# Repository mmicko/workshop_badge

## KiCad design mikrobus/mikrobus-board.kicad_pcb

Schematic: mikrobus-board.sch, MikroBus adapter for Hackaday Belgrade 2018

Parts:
J1: Conn_01x06; Pin_Header_Straight_1x06_Pitch2.54mm
P3, P5: microBus_1; Socket_Strip_Straight_1x08_Pitch2.54mm
P4, P6: microBus_2; Socket_Strip_Straight_1x08_Pitch2.54mm
UPDUINO2_DOWN1: Conn_01x16; Socket_Strip_Straight_1x16_Pitch2.54mm
UPDUINO2_UP1: Conn_01x18; Socket_Strip_Straight_1x18_Pitch2.54mm

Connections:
+3V3: J1.5, P3.7, P5.7, UPDUINO2_DOWN1.16
/AN_1: P3.1, UPDUINO2_UP1.1
/AN_2: P5.1, UPDUINO2_DOWN1.1
/CS_1: P3.3, UPDUINO2_UP1.6
/CS_2: P5.3, UPDUINO2_DOWN1.3
/EXT_1: J1.4, UPDUINO2_UP1.13
/EXT_2: J1.3, UPDUINO2_UP1.14
/EXT_3: J1.2, UPDUINO2_UP1.15
/EXT_4: J1.1, UPDUINO2_UP1.16
/INT_1: P4.2, UPDUINO2_UP1.8
/INT_2: P6.2, UPDUINO2_DOWN1.10
/MISO_1: P3.5, UPDUINO2_UP1.4
/MISO_2: P5.5, UPDUINO2_DOWN1.5
/MOSI_1: P3.6, UPDUINO2_UP1.3
/MOSI_2: P5.6, UPDUINO2_DOWN1.6
/OSC_OUT: UPDUINO2_DOWN1.9, UPDUINO2_UP1.17
/PWM_1: P4.1, UPDUINO2_UP1.7
/PWM_2: P6.1, UPDUINO2_DOWN1.8
/RST_1: P3.2, UPDUINO2_UP1.2
/RST_2: P5.2, UPDUINO2_DOWN1.2
/RX_1: P4.3, UPDUINO2_UP1.9
/RX_2: P6.3, UPDUINO2_DOWN1.11
/SCK_1: P3.4, UPDUINO2_UP1.5
/SCK_2: P5.4, UPDUINO2_DOWN1.4
/SCL_1: P4.5, UPDUINO2_UP1.11
/SCL_2: P6.5, UPDUINO2_DOWN1.13
/SDA_1: P4.6, UPDUINO2_UP1.12
/SDA_2: P6.6, UPDUINO2_DOWN1.14
/TX_1: P4.4, UPDUINO2_UP1.10
/TX_2: P6.4, UPDUINO2_DOWN1.12
GND: J1.6, P3.8, P4.8, P5.8, P6.8, UPDUINO2_DOWN1.15, UPDUINO2_UP1.18

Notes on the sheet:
mikroBus 1
mikroBus 2

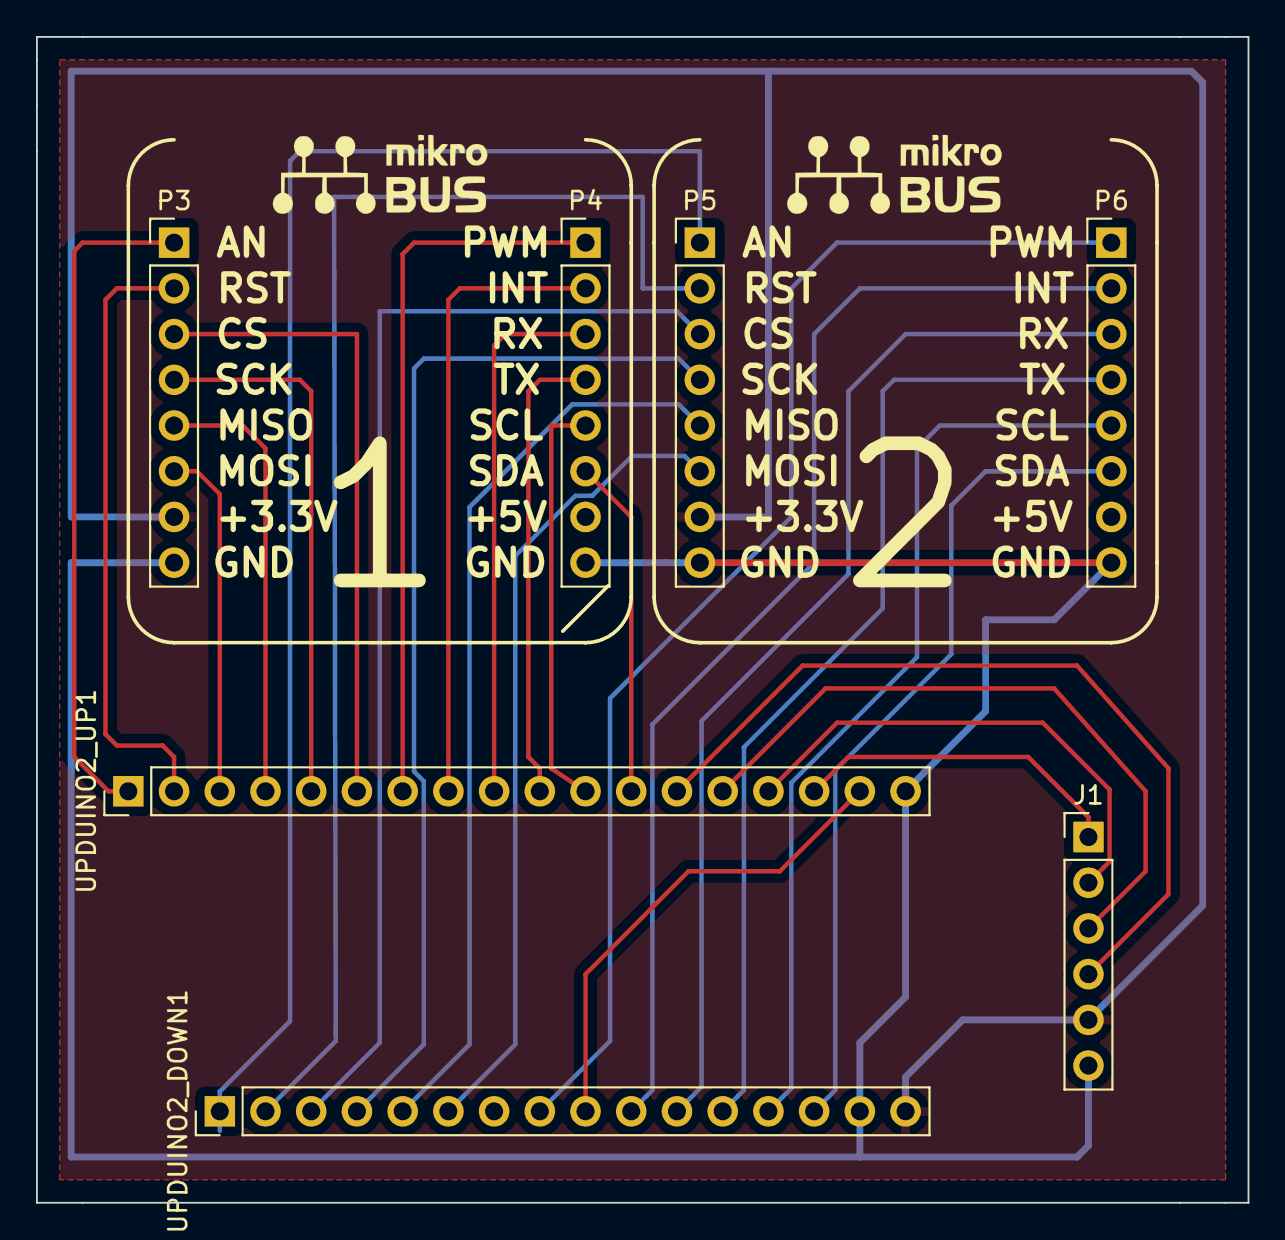
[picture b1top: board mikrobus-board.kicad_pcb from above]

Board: 2 copper layers, 67.3 x 64.8 mm, 9 parts (0 on the bottom side), 31 nets.

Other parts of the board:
G1, G1#2: LOGO; mikrobus

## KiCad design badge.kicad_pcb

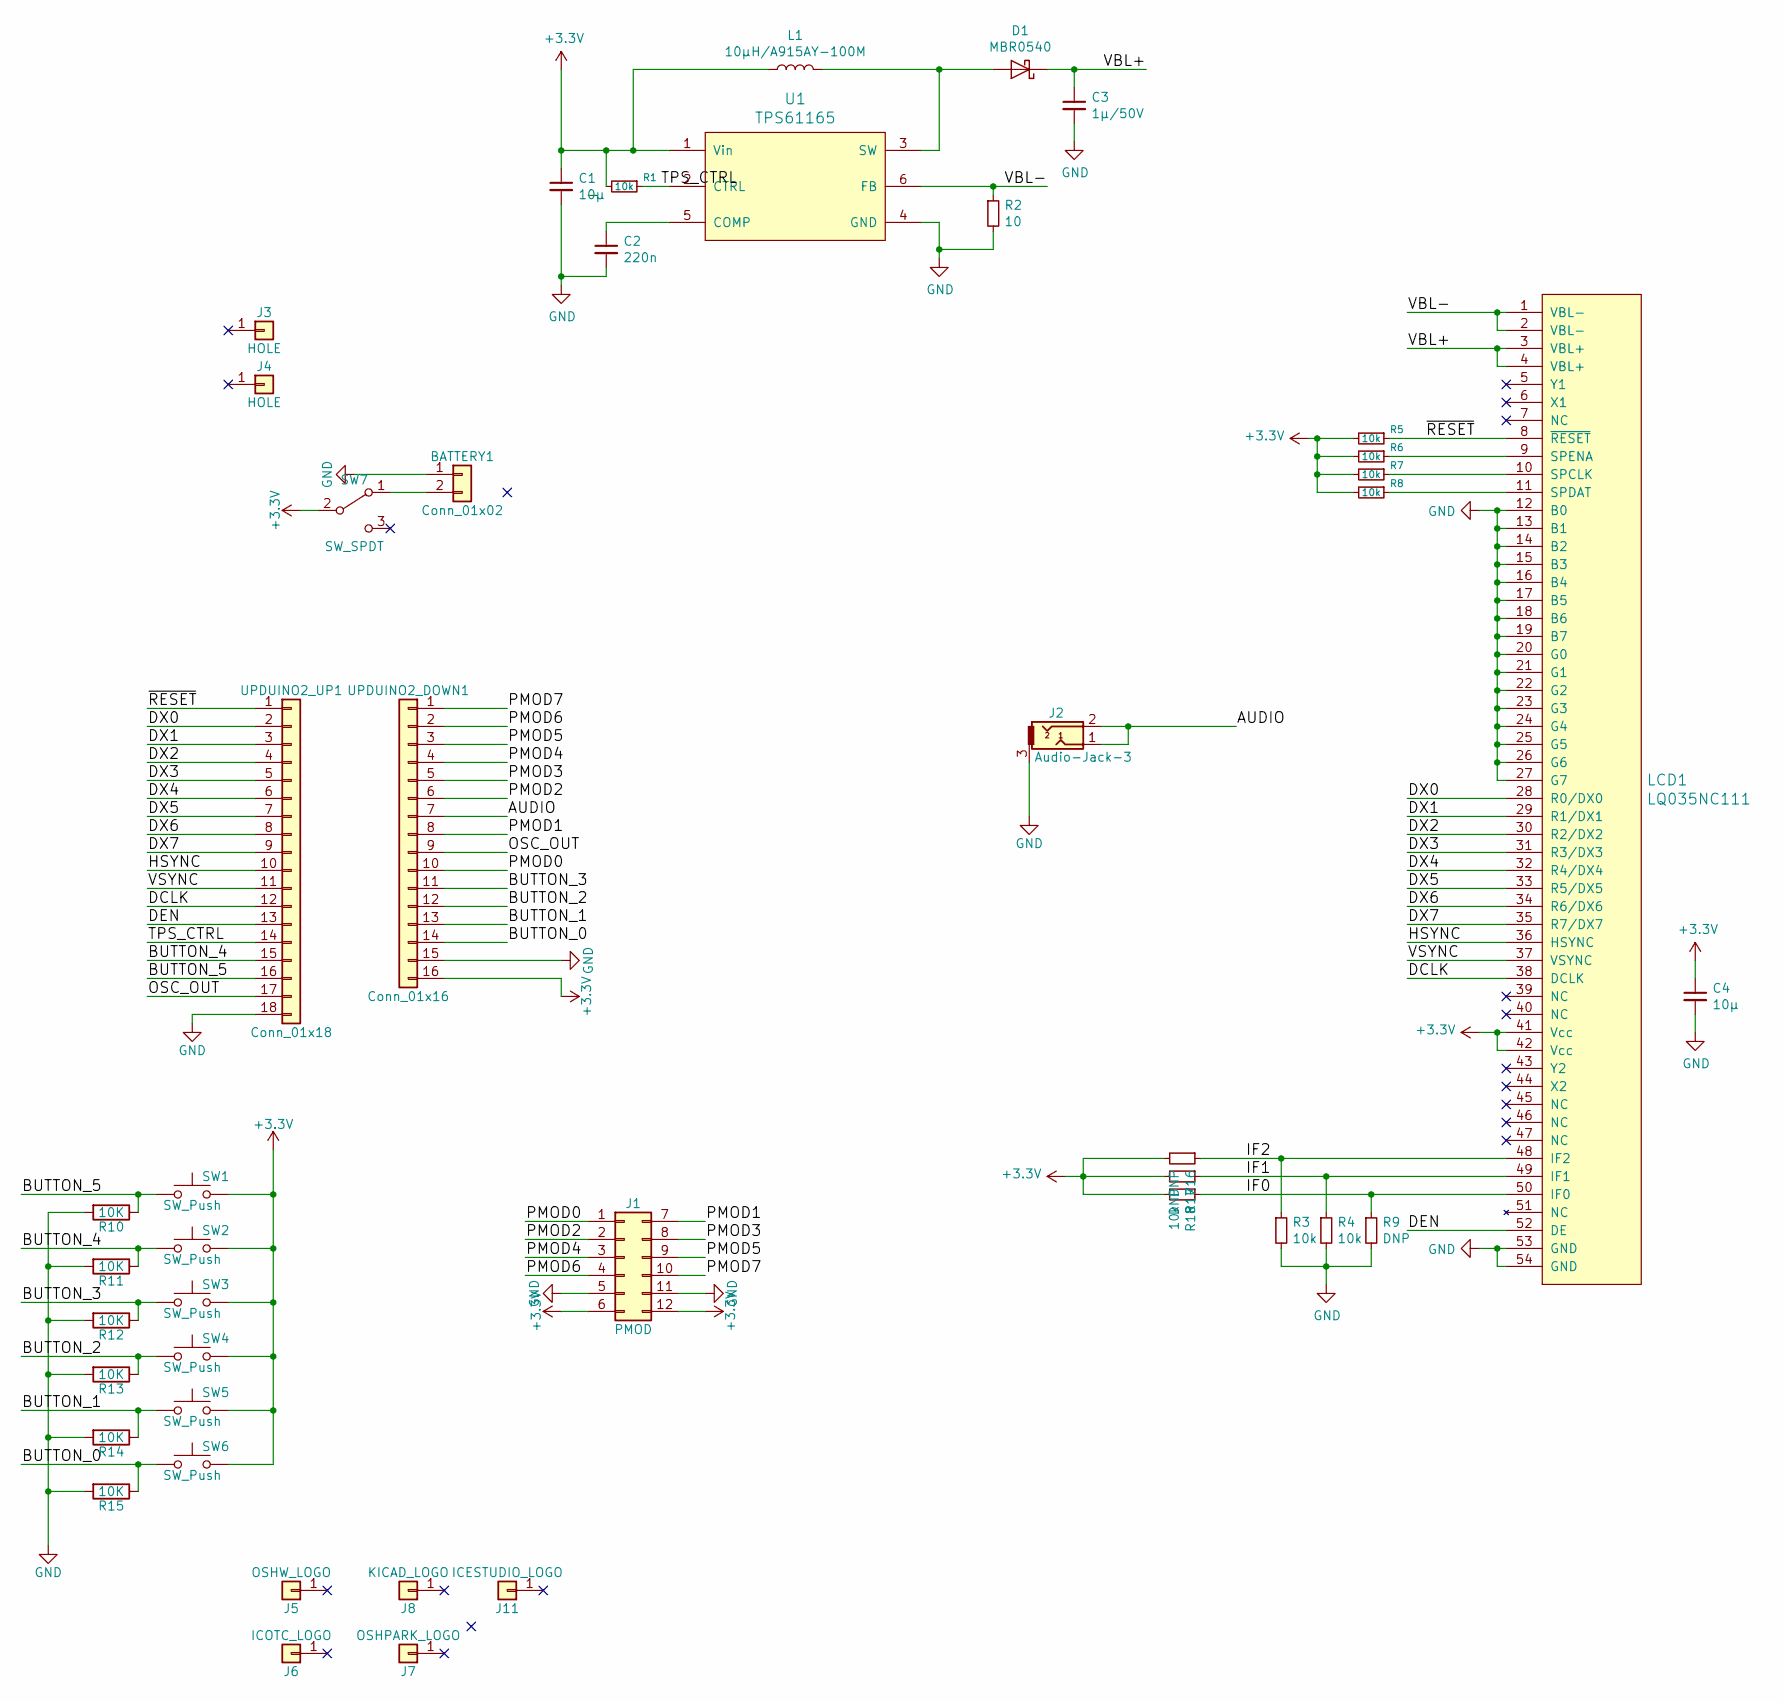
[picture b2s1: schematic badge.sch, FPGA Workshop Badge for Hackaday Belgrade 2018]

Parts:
BATTERY1: Conn_01x02; Pin_Header_Straight_1x02_Pitch2.54mm
C1, C4: 10µ; C_0805
C2: 220n; C_0603
C3: 1µ/50V; C_0805
D1: MBR0540; D_SOD-123
J1: PMOD; Pin_Header_Angled_2x06_Pitch2.54mm_PMOD
J2: Audio-Jack-3; AUDIO_JACK_3.5mm
J3, J4: HOLE; MountingHole_3.2mm_M3
J5: OSHW_LOGO; OSHW-Logo2_24.3x20mm_SilkScreen
J6: ICOTC_LOGO; ICOTC
J7: OSHPARK_LOGO; OSHPARK
J8: KICAD_LOGO; KiCad-Logo_12mm_SilkScreen
J11: ICESTUDIO_LOGO; ICESTUDIO
L1: 10µH/A915AY-100M; muRata_L_2020
LCD1: LQ035NC111; MOLEX_51296-5494_54pin_0.5mm_BTM
R1, R3, R4, R5, R6, R7, R8, R18: 10k; R_0603
R2: 10; R_0603
R9, R16, R17: DNP; R_0603
R10, R11, R12, R13, R14, R15: 10K; R_0603
SW1, SW2, SW3, SW4, SW5, SW6: SW_Push; SW_PUSH-12mm
SW7: SW_SPDT; SW_CuK_OS102011MA1QN1_SPDT_Angled
U1: TPS61165; SOT-23-6
UPDUINO2_DOWN1: Conn_01x16; Pin_Header_Straight_1x16_Pitch2.54mm
UPDUINO2_UP1: Conn_01x18; Pin_Header_Straight_1x18_Pitch2.54mm

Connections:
+3V3: C1.1, C4.1, J1.6, J1.12, L1.1, LCD1.41 (Vcc), LCD1.42 (Vcc), R1.2, R5.2, R6.2, R7.2, R8.2, R16.2, R17.2, R18.2, SW1.2, SW2.2, SW3.2, SW4.2, SW5.2, SW6.2, SW7.2 (B), U1.1 (Vin), UPDUINO2_DOWN1.16
/AUDIO: J2.1, J2.2, UPDUINO2_DOWN1.7
/BUTTON_0: R15.1, SW6.1, UPDUINO2_DOWN1.14
/BUTTON_1: R14.1, SW5.1, UPDUINO2_DOWN1.13
/BUTTON_2: R13.1, SW4.1, UPDUINO2_DOWN1.12
/BUTTON_3: R12.1, SW3.1, UPDUINO2_DOWN1.11
/BUTTON_4: R11.1, SW2.1, UPDUINO2_UP1.15
/BUTTON_5: R10.1, SW1.1, UPDUINO2_UP1.16
/DCLK: LCD1.38 (DCLK), UPDUINO2_UP1.12
/DEN: LCD1.52 (DE), UPDUINO2_UP1.13
/DX0: LCD1.28 (R0/DX0), UPDUINO2_UP1.2
/DX1: LCD1.29 (R1/DX1), UPDUINO2_UP1.3
/DX2: LCD1.30 (R2/DX2), UPDUINO2_UP1.4
/DX3: LCD1.31 (R3/DX3), UPDUINO2_UP1.5
/DX4: LCD1.32 (R4/DX4), UPDUINO2_UP1.6
/DX5: LCD1.33 (R5/DX5), UPDUINO2_UP1.7
/DX6: LCD1.34 (R6/DX6), UPDUINO2_UP1.8
/DX7: LCD1.35 (R7/DX7), UPDUINO2_UP1.9
/HSYNC: LCD1.36 (HSYNC), UPDUINO2_UP1.10
/IF0: LCD1.50 (IF0), R9.1, R18.1
/IF1: LCD1.49 (IF1), R4.1, R17.1
/IF2: LCD1.48 (IF2), R3.1, R16.1
/OSC_OUT: UPDUINO2_DOWN1.9, UPDUINO2_UP1.17
/PMOD0: J1.1, UPDUINO2_DOWN1.10
/PMOD1: J1.7, UPDUINO2_DOWN1.8
/PMOD2: J1.2, UPDUINO2_DOWN1.6
/PMOD3: J1.8, UPDUINO2_DOWN1.5
/PMOD4: J1.3, UPDUINO2_DOWN1.4
/PMOD5: J1.9, UPDUINO2_DOWN1.3
/PMOD6: J1.4, UPDUINO2_DOWN1.2
/PMOD7: J1.10, UPDUINO2_DOWN1.1
/TPS_CTRL: R1.1, U1.2 (CTRL), UPDUINO2_UP1.14
/VBL+: C3.1, D1.1 (K), LCD1.3 (VBL+), LCD1.4 (VBL+)
/VBL-: LCD1.1 (VBL-), LCD1.2 (VBL-), R2.1, U1.6 (FB)
/VSYNC: LCD1.37 (VSYNC), UPDUINO2_UP1.11
/~RESET: LCD1.8 (~RESET), R5.1, UPDUINO2_UP1.1
GND: BATTERY1.1, C1.2, C2.2, C3.2, C4.2, J1.5, J1.11, J2.3, LCD1.12 (B0), LCD1.13 (B1), LCD1.14 (B2), LCD1.15 (B3), LCD1.16 (B4), LCD1.17 (B5), LCD1.18 (B6), LCD1.19 (B7), LCD1.20 (G0), LCD1.21 (G1), LCD1.22 (G2), LCD1.23 (G3), LCD1.24 (G4), LCD1.25 (G5), LCD1.26 (G6), LCD1.27 (G7), LCD1.53 (GND), LCD1.54 (GND), R2.2, R3.2, R4.2, R9.2, R10.2, R11.2, R12.2, R13.2, R14.2, R15.2, U1.4 (GND), UPDUINO2_DOWN1.15, UPDUINO2_UP1.18
unnamed: BATTERY1.2, SW7.1 (A)
unnamed: C2.1, U1.5 (COMP)
unnamed: D1.2 (A), L1.2, U1.3 (SW)
unnamed: LCD1.9 (SPENA), R6.1
unnamed: LCD1.10 (SPCLK), R7.1
unnamed: LCD1.11 (SPDAT), R8.1

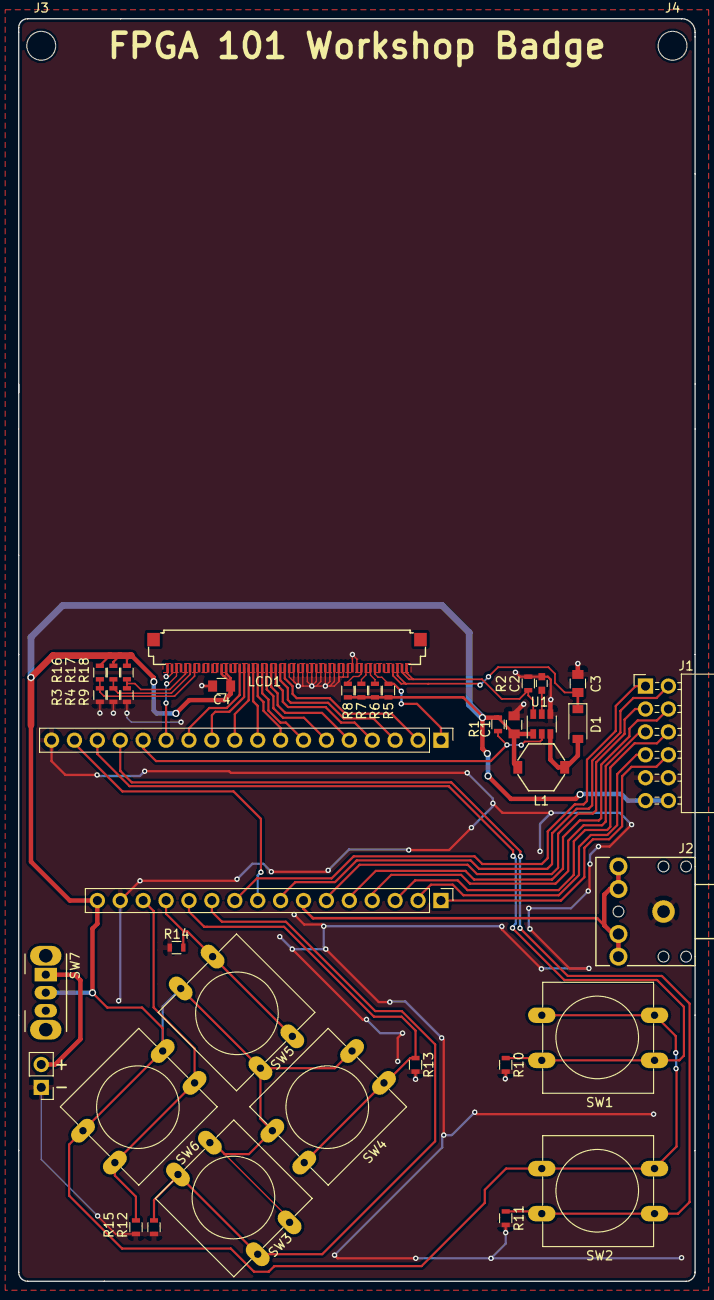
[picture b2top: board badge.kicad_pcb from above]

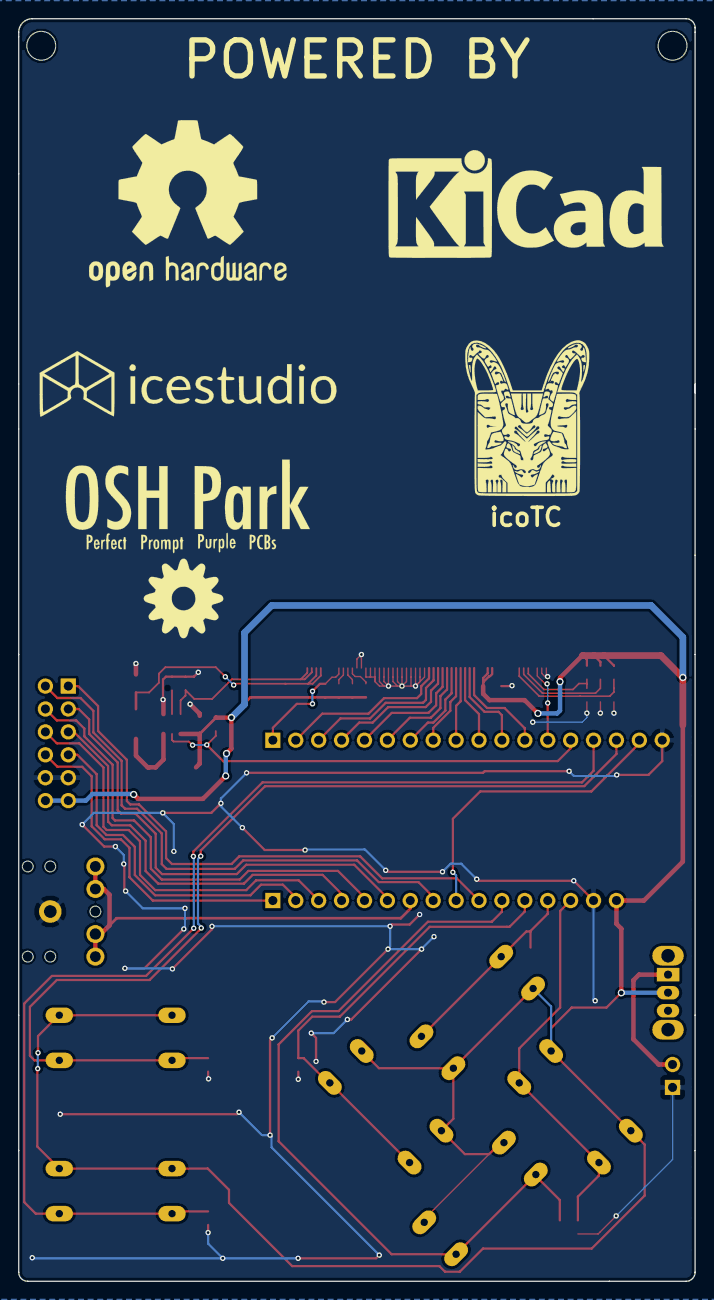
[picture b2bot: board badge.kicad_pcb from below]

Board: 2 copper layers, 75.0 x 140.0 mm, 45 parts (5 on the bottom side), 43 nets.

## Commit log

2018-02-10 Added initial schematics, import part from David PMOD LCD35 project
2018-02-10 Make extension half pmod, and left one led, added battery switch.
2018-02-10 removed SPI on LED to optimize, drive TPS control, 2 leds on dedicated PLL ports
2018-02-10 Made audio mono and using pin 37, change port to PMOD, clk on proper pin,
2018-02-10 Footprint assignments and initial placement
2018-02-11 Routing done and logos added
2018-02-12 Final tweaks, create gerbers
2018-03-03 Add LCD test and PCF file
2018-03-28 Added initial mikroBus board design
2018-03-28 update connector
2018-03-28 better placing
2018-03-28 Finished routing
2018-03-29 Simpler routing
2018-03-29 Power lines and better routing for power lines
2018-03-29 Finished design
2018-03-29 Fixed silk
2018-03-29 Added gerber files for mikrobus board
2018-05-17 Remove files not belonging here
